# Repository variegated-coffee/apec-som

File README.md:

# All Purpose Espresso Controller System-on-Module

*APEC SoM R1A, rendered in KiCad.*

Espresso electronics are usually proprietary affairs with little to no expandability. The purpose of this project is to give everyone an open source alternative with lots of features and flexibility. 

The APEC SoM is a 104 pin, 1.27 mm pitch compact castellated module containing pretty much everything you need to build an espresso machine controller. The module is intended to be paired with a machine specific carrier board, containing things like connectors, FETs and passives.

## High-level features

* RP2350B microcontroller with 8 MB of program flash, 8 MB of settings flash and 8 MB PSRAM
* ESP32-C6 for Wi-fi/Bluetooth/Zigbee/Thread connectivity
* ADS124S08 ADC
* FDC1004 Capacitance-to-digital
* Five different power domains
  * Vin (6-17V)
  * 6V
  * 5VD
  * 5VA
  * 3V3
* 4-port USB 2.0 hub
  * One port each used for RP2350B and ESP32-C6
  * Recommendation: Use one of the other ports for a [Femtoprobe](https://github.com/variegated-coffee/femtoprobe)

## Project status

The current hardware revision is R1A. It hasn't been manufactured yet, and you shouldn't be the first one to do it. The earlier engineering validation revisions, EV1 and EV2, have been manufactured; [CHANGELOG.md](CHANGELOG.md) lists what changed between revisions.

## ⚠️ Safety warning

This project is a module intended for use as a component in a controller
for an espresso machine. Espresso machines typically use mains voltage,
high-pressure hot water and steam. Mistakes in designing, building, wiring,
or programming a controller or machine around this module can cause
electric shock, fire, burns, or scalding.

This module is not a safety component. Safety-critical protections, such
as thermal cutouts and pressure relief, must be implemented independently
of this module and its firmware. Only build or use it if you are competent
with mains electrical work and pressurised systems, and follow local
electrical regulations.

## Notice

This repository contains design files only. It is not a finished product, and it has not been tested or certified for compliance with any regulation, including but not limited to CE, UKCA or FCC requirements.

Anyone who manufactures, assembles, or places a product based on these files on the market does so as the manufacturer of that product, and is solely responsible for its safety, conformity assessment, marking, documentation, and any legal obligations that follow. If you build or use it yourself, you do so at your own risk.

The module includes a 2.4 GHz radio transceiver (ESP32-C6). Products using it are subject to radio equipment regulations in addition to other applicable requirements.

The designs are provided “as is” under the CERN-OHL-P v2. See sections 5.1 and 5.2 for the disclaimer of warranty and limitation of liability.

## License

The design files and documentation in this repository are licensed under the CERN Open Hardware Licence Version 2 – Permissive (CERN-OHL-P-2.0); see [LICENSE.txt](LICENSE.txt). This includes the carrier-board symbol and footprints (`APEC_SoM.kicad_sym` and `APEC_SoM.pretty`), so you can use them in your own carrier designs.

Some library files come from third parties and keep their own licences; see [THIRD_PARTY.md](THIRD_PARTY.md).

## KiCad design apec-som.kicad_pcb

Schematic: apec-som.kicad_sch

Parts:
C1, C5, C53: 6.8 nF, 25V, X7R; C_0201_0603Metric; LCSC C385027
C2, C6: 10 μF, 50 V, X7R; C_1206_3216Metric; LCSC C89632
C3, C7, C14, C16, C17, C18, C19, C20, C21, C22, C24, C42, C45, C55, C56, C57, C59, C64: 100 nF, 16V, X7S; C_0201_0603Metric; LCSC C85923
C4, C8, C43, C49, C50: 22 uF, 25V, X5R; C_0805_2012Metric; LCSC C86816
C9, C10: 15 pF, C0G; C_0201_0603Metric; LCSC C85891
C11, C12: 4.7µF, 10V, X5R, GRM155R61A475MEAAD; C_0402_1005Metric_small_pads; LCSC C335105
C13, C15: 4.7µF, 10V, X5R, GRM155R61A475MEAAD; C_0402_1005Metric; LCSC C335105
C23, C27: 100 nF, 16V, X7S; C_0201_0603Metric; JLCPCB Basic N
C25, C46, C47, C51, C54, C62, C65: 1 uF, 16V, X5R; C_0201_0603Metric; LCSC C335102
C36, C58: 1 uF, 16V, X5R; C_0201_0603Metric; JLCPCB Basic N
C60: 10 nF, 25V, X7R; C_0201_0603Metric; LCSC C326875
C61, C63: 10 uF, 10V, X5R; C_0603_1608Metric; LCSC C77044
FID1, FID2, FID3, FID4: Fiducial; Fiducial_1mm_Mask2mm
J1: APEC_SoM_Castellations_53-86
J2: APEC_SoM_Castellations_01-34
J6: APEC_SoM_Castellations_87-104
J7: APEC_SoM_Castellations_35-52
L1: AOTA-B201610S3R3-101-T; L_pol_2016; LCSC C42411119
LOGO1: OSHW logo; OSHW-Logo_5.7x6mm_SilkScreen
LOGO2: APEC logo; APECLogo_Micro
LOGO3: Variegated Coffee logo; VariegatedCoffeeLogo_Micro
MB1, MB2, MB3, MB4: Mousebite cross; mouse-bite-5mm-cross
MB5, MB6, MB7, MB8: Mousebite line; mouse-bite-5mm-line
Q7: NTZD3154NT1G; SOT-563; LCSC C145189
R1, R2, R4, R5, R21, R22, R24, R31: 10K; R_0201_0603Metric; LCSC C106225
R3, R23, R25: 1K; R_0201_0603Metric; LCSC C131396
R6, R20: 100K; R_0201_0603Metric; LCSC C270364
R7, R9: 75K, 0.5%; R_0201_0603Metric; LCSC C851792
R8: 12.1K, 1%; R_0201_0603Metric; LCSC C180296
R10: 24K, 0.5%; R_0201_0603Metric; LCSC C851691
R11, R12: 27R; R_0201_0603Metric; LCSC C273268
R13, R15: 1K5; R_0201_0603Metric; LCSC C155737
R14: 10K; R_0201_0603Metric; JLCPCB Basic Y
R16: 43K, 1%; R_0201_0603Metric; LCSC C138142
R17, R18, R55: 10K; R_0201_0603Metric; JLCPCB Basic N
R19: 8K2, 1%; R_0201_0603Metric; LCSC C274879
R44: 2K7 1%; R_0201_0603Metric; LCSC C273271
R45, R46, R47, R48, R49: 47R; R_0201_0603Metric; LCSC C273279
R54: 33R; R_0201_0603Metric; LCSC C295794
TP1, TP2, TP3, TP4, TP5, TP6, TP7, TP8: TestPoint_Flag; TestPoint_Pad_D1.0mm
U1, U3: TPS82130; Texas_SIL0008D_MicroSiP-8-1EP_2.8x3mm_P0.65mm_EP1.1x1.9mm_T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; LCSC C473914
U2, U9: W25Q64JVXGIQ; XSON-8-1EP_4x4mm_P0.8mm_EP2.39x3.1mm; LCSC C2940195
U4: RP2350B; RP2350-QFN-80-1EP_10x10_P0.4mm_EP3.4x3.4mm_ThermalVias; LCSC C42415655
U5: FE1.1s; QFN-24-1EP_4x4mm_P0.5mm_EP2.5x2.5mm; LCSC C6776948
U6: ADS124S08IPBSR; LQFP-32_5x5mm_P0.5mm; LCSC C2870171
U7: ESP32-C6-MINI-1/U; ESP32-C6-MINI-1U; LCSC C7558096
U10: FDC1004; VSSOP-10_3x3mm_P0.5mm; LCSC C2865994
U11: NCP59800BMNADJTAG; DFN-8-1EP_3x3mm_P0.65mm_EP1.6x1.85mm; LCSC C464053
U12: APS6404L-3SQR; USON-8-1EP_3x2mm_P0.5mm_EP0.3x1.7mm; LCSC C3040877
U13: ADM7170ACPZ-5.0-R7; SON50P300X300X80-9N; PARTREV D; LCSC C658474
U14: 74LVC2G125; VSSOP-8_2.4x2.1mm_P0.5mm; LCSC C548582
U15: 74LVC1G240; SOT-353_SC-70-5; LCSC C470957
Y1: ABM8-272-T3; Crystal_SMD_3225-4Pin_3.2x2.5mm; LCSC C20625731
Y3: 12MHz, 20pF; Crystal_SMD_3225-4Pin_3.2x2.5mm; LCSC C133334

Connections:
3V3_PG: R1.1, U1.1 (EN), U3.7 (PG), U11.5 (EN), U13.5 (EN)
+1V1: C12.1, C14.1, C15.1, C16.1, L1.1, U4.10 (DVDD), U4.32 (DVDD), U4.51 (DVDD), U4.65 (VREG_FB)
+3V3: C3.2, C7.2, C8.1, C11.1, C17.1, C18.1, C19.1, C20.1, C21.1, C22.1, C23.2, C24.1, C25.1, C27.2, C42.2, C43.2, C45.1, C50.1, C55.1, C56.1, C57.1, C58.2, C62.1, C64.2, J1.76, J1.77, R1.2, R2.1, R4.2, R5.2, R9.1, R14.1, R17.2, R18.2, R21.1, R22.2, R24.1, R31.2, R54.1, R55.2, U2.3 (~WP/IO2), U2.7 (~HOLD/IO3), U2.8 (VCC), U3.4 (VOUT), U3.5 (VOUT), U4.5 (IOVDD), U4.15 (IOVDD), U4.24 (IOVDD), U4.29 (IOVDD), U4.41 (IOVDD), U4.50 (IOVDD), U4.59 (ADC_AVDD), U4.60 (IOVDD), U4.64 (VREG_VIN), U4.68 (USB_OTP_VDD), U4.69 (QSPI_IOVDD), U4.76 (IOVDD), U5.1 (OVCJ), U5.18 (BUSJ), U5.20 (VD33F), U6.15 (IOVDD), U6.16 (DVDD), U6.18 (RESET_N), U7.3 (3V3), U9.8 (VCC), U10.8 (VDD), U12.8 (VCC), U14.8 (VCC), U15.5 (VCC)
+5V: C61.1, C65.2, J1.85, J1.86, R16.1, U11.1 (OUT), U11.2 (OUT)
+5VA: C46.1, C54.2, C63.1, J7.50, U6.26 (AVDD), U13.1 (VOUT), U13.2 (VOUT), U13.3 (SENSE)
+6V: C4.1, C49.1, C51.1, C59.2, J1.82, J1.83, R7.1, U1.4 (VOUT), U1.5 (VOUT), U11.7 (IN), U11.8 (IN), U13.7 (VIN), U13.8 (VIN)
/RP2040_USB_POST_R_DN: R12.1, U5.5 (DM4)
/RP2040_USB_POST_R_DP: R11.1, U5.6 (DP4)
ADC_AIN0: J7.41, U6.7 (AIN0)
ADC_AIN1: J7.42, U6.6 (AIN1)
ADC_AIN2: J7.43, U6.5 (AIN2)
ADC_AIN3: J7.44, U6.4 (AIN3)
ADC_AIN4: J7.45, U6.3 (AIN4)
ADC_AIN5: J7.46, U6.2 (AIN5)
ADC_AIN6: J7.47, U6.32 (REFP1_AIN6)
ADC_AIN7: J7.48, U6.31 (REFN1_AIN7)
ADC_AIN8: J1.53, U6.22 (GPIO0_AIN8)
ADC_AIN9: J1.54, U6.21 (GPIO1_AIN9)
ADC_AIN10: J1.55, U6.20 (GPIO2_AIN10)
ADC_AIN11: J1.56, U6.19 (GPIO3_AIN11)
ADC_CS: R24.2, R49.2, TP5.1 (1_1), U4.40 (GPIO32)
ADC_DRDY: R45.2, TP6.1 (1_1), U4.37 (GPIO29)
ADC_REFN0: J7.52, U6.29 (REFN0)
ADC_REFP0: J7.51, U6.30 (REFP0)
CIN1: J7.39, U10.2 (CIN1)
CIN2: J7.38, U10.3 (CIN2)
CIN3: J7.37, U10.4 (CIN3)
CIN4: J7.36, U10.5 (CIN4)
C_SHIELD_1: J7.40, U10.1 (SHLD1)
C_SHIELD_2: J7.35, U10.6 (SHLD2)
ESP32_BOOTSEL_RP2040: Q7.2 (G1), R15.2, U7.28 (GPIO22)
ESP32_DISABLE_RP2040: Q7.5 (G2), R13.2, U7.29 (GPIO23)
ESP32_EN: C36.2, J6.104, R14.2, U7.8 (EN/CHIP_PU)
ESP32_GP0: J2.1, U7.12 (GPIO0/ADC1_CH0/XTAL_32K_P)
ESP32_GP1: J2.2, U7.13 (GPIO1/ADC1_CH1/XTAL_32K_N)
ESP32_GPIO9: J6.103, U7.23 (GPIO9)
ESP32_JTAG_SELECT: J6.102, U7.20 (GPIO15)
ESP32_TCK: J6.99, U7.15 (MTCK/GPIO6/ADC1_CH6)
ESP32_TDI: J6.100, U7.10 (MTDI/GPIO5/ADC1_CH5)
ESP32_TDO: J6.98, U7.16 (MTDO/GPIO7)
ESP32_TMS: J6.101, U7.9 (MTMS/GPIO4/ADC1_CH4)
ESP32_U0RXD: J2.3, U7.30 (U0RXD/GPIO17)
ESP32_U0TXD: J2.4, U7.31 (U0TXD/GPIO16)
ESP32_USB_DN: U5.7 (DM3), U7.17 (GPIO12/USB_D-)
ESP32_USB_DP: U5.8 (DP3), U7.18 (GPIO13/USB_D+)
ESP_RP_UART_BOOT_ENn: R5.1, U7.19 (GPIO14), U14.1, U14.7, U15.1, U15.2
ESP_RP_UART_BOOT_UART_RX: U7.5 (GPIO2/ADC1_CH2), U14.5
ESP_RP_UART_BOOT_UART_TX: U7.6 (GPIO3/ADC1_CH3), U14.6
FLASH2_SS: R55.1, TP8.1 (1_1), U4.77 (GPIO0), U12.1 (~CS)
INT_SPI_MISO: J1.58, R46.2, U2.2 (SO/IO1), U4.36 (GPIO28)
INT_SPI_MOSI: J1.60, R48.2, U2.5 (SI/IO0), U4.39 (GPIO31)
INT_SPI_SCLK: J1.59, R47.2, U2.6 (SCK), U4.38 (GPIO30)
unnamed: C10.1, R3.1, Y1.1
unnamed: Q7.6 (D1), R23.1
unnamed: R7.2, R8.2, U1.6 (FB)
unnamed: C1.1, U1.8 (SS/TR)
unnamed: R9.2, R10.2, U3.6 (FB)
unnamed: C5.1, U3.8 (SS/TR)
unnamed: C13.1, R54.2, U4.61 (VREG_AVDD)
unnamed: L1.2, U4.63 (VREG_LX)
unnamed: C9.1, U4.30 (XIN), Y1.3
unnamed: R3.2, U4.31 (XOUT)
unnamed: R20.1, U5.21 (DRV)
unnamed: R44.2, U5.13 (REXT)
unnamed: U5.4 (XIN), Y3.1
unnamed: U5.3 (XOUT), Y3.3
unnamed: R31.1, U5.16 (~XRSTJ)
unnamed: R49.1, U6.9 (CS_N)
unnamed: R48.1, U6.10 (DIN)
unnamed: R46.1, U6.12 (DOUT_DRDY_N)
unnamed: R45.1, U6.13 (DRDY_N)
unnamed: C47.1, U6.23 (REFOUT)
unnamed: R47.1, U6.11 (SCLK)
unnamed: R22.1, U7.22 (GPIO8)
unnamed: R16.2, R19.2, U11.3 (FB/SNS)
unnamed: C60.1, U11.6 (NR)
unnamed: C53.1, U13.4 (SS)
QWIIC_SCL: J2.33, R2.2, U4.48 (GPIO39), U10.9 (SCL)
QWIIC_SDA: J2.34, R4.1, U4.47 (GPIO38), U10.10 (SDA)
RP2040_BOOTSEL: R17.1, R23.2, R25.2, U4.75 (QSPI_SS), U9.1 (~CS)
RP2040_BOOTSEL_EXT: J1.69, R25.1
RP2040_QSPI_SCK: U4.71 (QSPI_SCLK), U9.6 (SCK), U12.6 (SCK)
RP2040_QSPI_SD0: U4.72 (QSPI_SD0), U9.5 (SI/IO0), U12.5 (SI/IO0)
RP2040_QSPI_SD1: U4.74 (QSPI_SD1), U9.2 (SO/IO1), U12.2 (SO/IO1), U15.4
RP2040_QSPI_SD2: U4.73 (QSPI_SD2), U9.3 (~WP/IO2), U12.3 (~WP/IO2), U14.2
RP2040_QSPI_SD3: U4.70 (QSPI_SD3), U9.7 (~HOLD/IO3), U12.7 (~HOLD/IO3), U14.3
RP2040_RESETn: J1.66, Q7.3 (D2), R18.1, U4.35 (RUN)
RP2040_SWCLK: J1.68, U4.33 (SWCLK)
RP2040_SWD: J1.67, U4.34 (SWD)
RP2040_USB_PRE_R_DN: R12.2, U4.66 (USB_DM)
RP2040_USB_PRE_R_DP: R11.2, U4.67 (USB_DP)
RP_ESP_UART_CTS: TP2.1 (1_1), U4.8 (GPIO10), U7.25 (GPIO19)
RP_ESP_UART_RTS: TP1.1 (1_1), U4.9 (GPIO11), U7.24 (GPIO18)
RP_ESP_UART_RX: TP3.1 (1_1), U4.7 (GPIO9), U7.26 (GPIO20)
RP_ESP_UART_TX: TP4.1 (1_1), U4.6 (GPIO8), U7.27 (GPIO21)
RP_GP1: J2.23, U4.78 (GPIO1)
RP_GP2: J2.22, U4.79 (GPIO2)
RP_GP3: J2.21, U4.80 (GPIO3)
RP_GP4: J2.20, U4.1 (GPIO4)
RP_GP5: J2.19, U4.2 (GPIO5)
RP_GP6: J2.18, U4.3 (GPIO6)
RP_GP7: J2.17, U4.4 (GPIO7)
RP_GP12: J2.16, U4.11 (GPIO12)
RP_GP13: J2.15, U4.12 (GPIO13)
RP_GP14: J2.14, U4.13 (GPIO14)
RP_GP15: J2.13, U4.14 (GPIO15)
RP_GP16: J2.12, U4.16 (GPIO16)
RP_GP17: J2.11, U4.17 (GPIO17)
RP_GP18: J2.10, U4.18 (GPIO18)
RP_GP19: J2.9, U4.19 (GPIO19)
RP_GP20: J2.8, U4.20 (GPIO20)
RP_GP21: J2.7, U4.21 (GPIO21)
RP_GP22: J2.6, U4.22 (GPIO22)
RP_GP23: J1.73, U4.23 (GPIO23)
RP_GP24: J1.72, U4.25 (GPIO24)
RP_GP25: J1.71, U4.26 (GPIO25)
RP_GP26: J1.70, U4.27 (GPIO26)
RP_GP33: J1.65, U4.42 (GPIO33)
RP_GP34: J1.64, U4.43 (GPIO34)
RP_GP35: J1.63, U4.44 (GPIO35)
RP_GP36: J1.62, U4.45 (GPIO36)
RP_GP37: J1.61, U4.46 (GPIO37)
RP_GP40: J2.32, U4.49 (GPIO40_ADC0)
RP_GP41: J2.31, U4.52 (GPIO41_ADC1)
RP_GP42: J2.30, U4.53 (GPIO42_ADC2)
RP_GP43: J2.29, U4.54 (GPIO43_ADC3)
RP_GP44: J2.28, U4.55 (GPIO44_ADC4)
RP_GP45: J2.27, U4.56 (GPIO45_ADC5)
RP_GP46: J2.26, U4.57 (GPIO46_ADC6)
RP_GP47: J2.25, U4.58 (GPIO47_ADC7)
SET_FLSH_CS: R21.2, TP7.1 (1_1), U2.1 (~CS), U4.28 (GPIO27)
USB_PORT3_DN: J6.92, U5.11 (DM1)
USB_PORT3_DP: J6.91, U5.12 (DP1)
USB_PORT4_DN: J6.95, U5.9 (DM2)
USB_PORT4_DP: J6.94, U5.10 (DP2)
USB_UPSTREAM_DN: J6.89, U5.14 (DMU)
USB_UPSTREAM_DP: J6.88, U5.15 (DPU)
USB_VBUS: J6.87, R6.1, U5.17 (VBUSM)

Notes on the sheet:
Fiducials, mousebites and logos are board-only items.
Power Management 6V @ 3A (sequenced after 3V3 PG) 3V3 @ 3A 5V @ 1A (powered by 6V) 5VA @ 500mA (powered by 6V)
Vo = 0.8 * (1 + R1/R2) = 0.8 * (1 + 75k/24k) = 3.3 V
ESP32 Debug (Optional)
Panelization and board graphics
Has to be at least 330 nF according to DS, pg. 98.
RP2040 Debug (optional)
Vo = 0.8 * (1 + R1/R2) = 0.8 * (1 + 75k/12.1k) = 5.76 V
ESP32 QWIIC Connector (Optional)
UART1
RP2040 QWIIC Connector (Optional)
RP2040 MCU and Flash
Originally specced as 5.6 nF Switched to 6.8 nF, because it's available as JLCPCB Basic Part Changes start-up time from 2.8 ms to 3.4 ms
Recommended value is 1 nF, but since I'm not using that value anywhere else, I'm instead picking 6.8 nf, which brings startup time from 1 ms to 4.46 ms.
They have symbols here so Update PCB from Schematic keeps them.
I2C1
FDC1004 Capacitance-to-Digital (Optional)
ESP32-C6 control of RP2350
SPI1

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
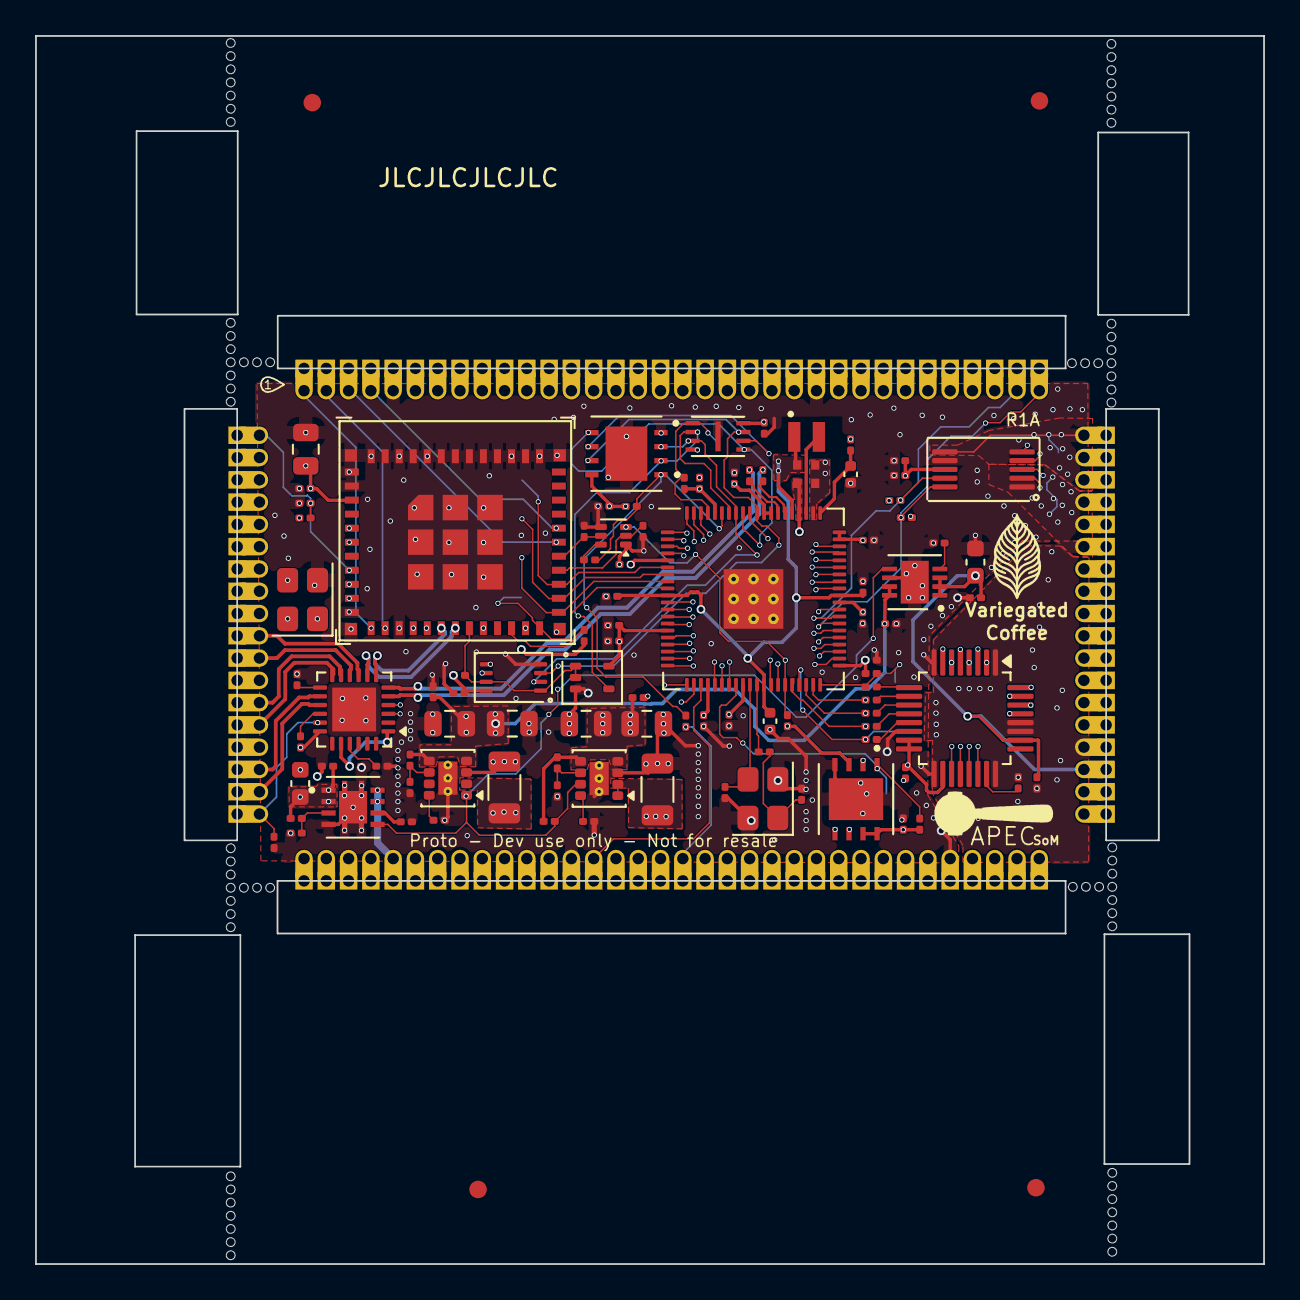
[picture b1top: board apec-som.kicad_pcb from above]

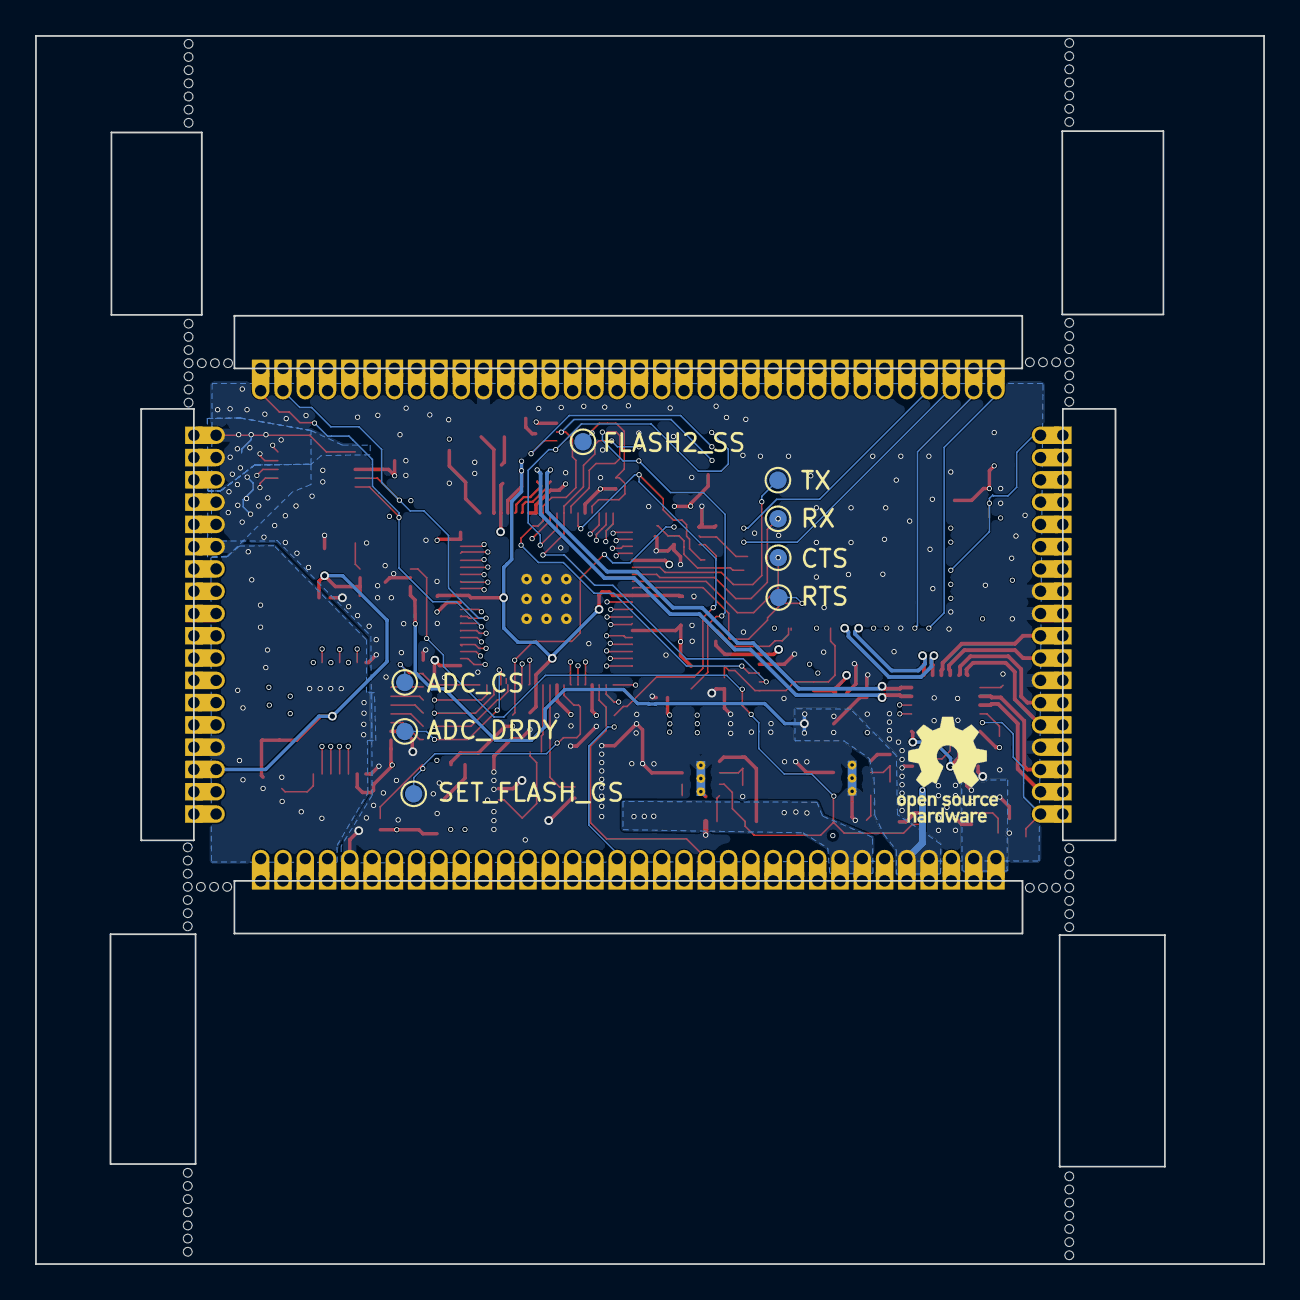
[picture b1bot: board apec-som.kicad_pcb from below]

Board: 6 copper layers, 70.0 x 70.0 mm, 127 parts (9 on the bottom side), 140 nets.

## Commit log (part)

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2025-03-27 As manufactured for EV1
2025-03-30 EV1 as manufactured
2025-06-19 EV2 changes to make manufacturing easier
2025-09-02 As manufactured for EV2
